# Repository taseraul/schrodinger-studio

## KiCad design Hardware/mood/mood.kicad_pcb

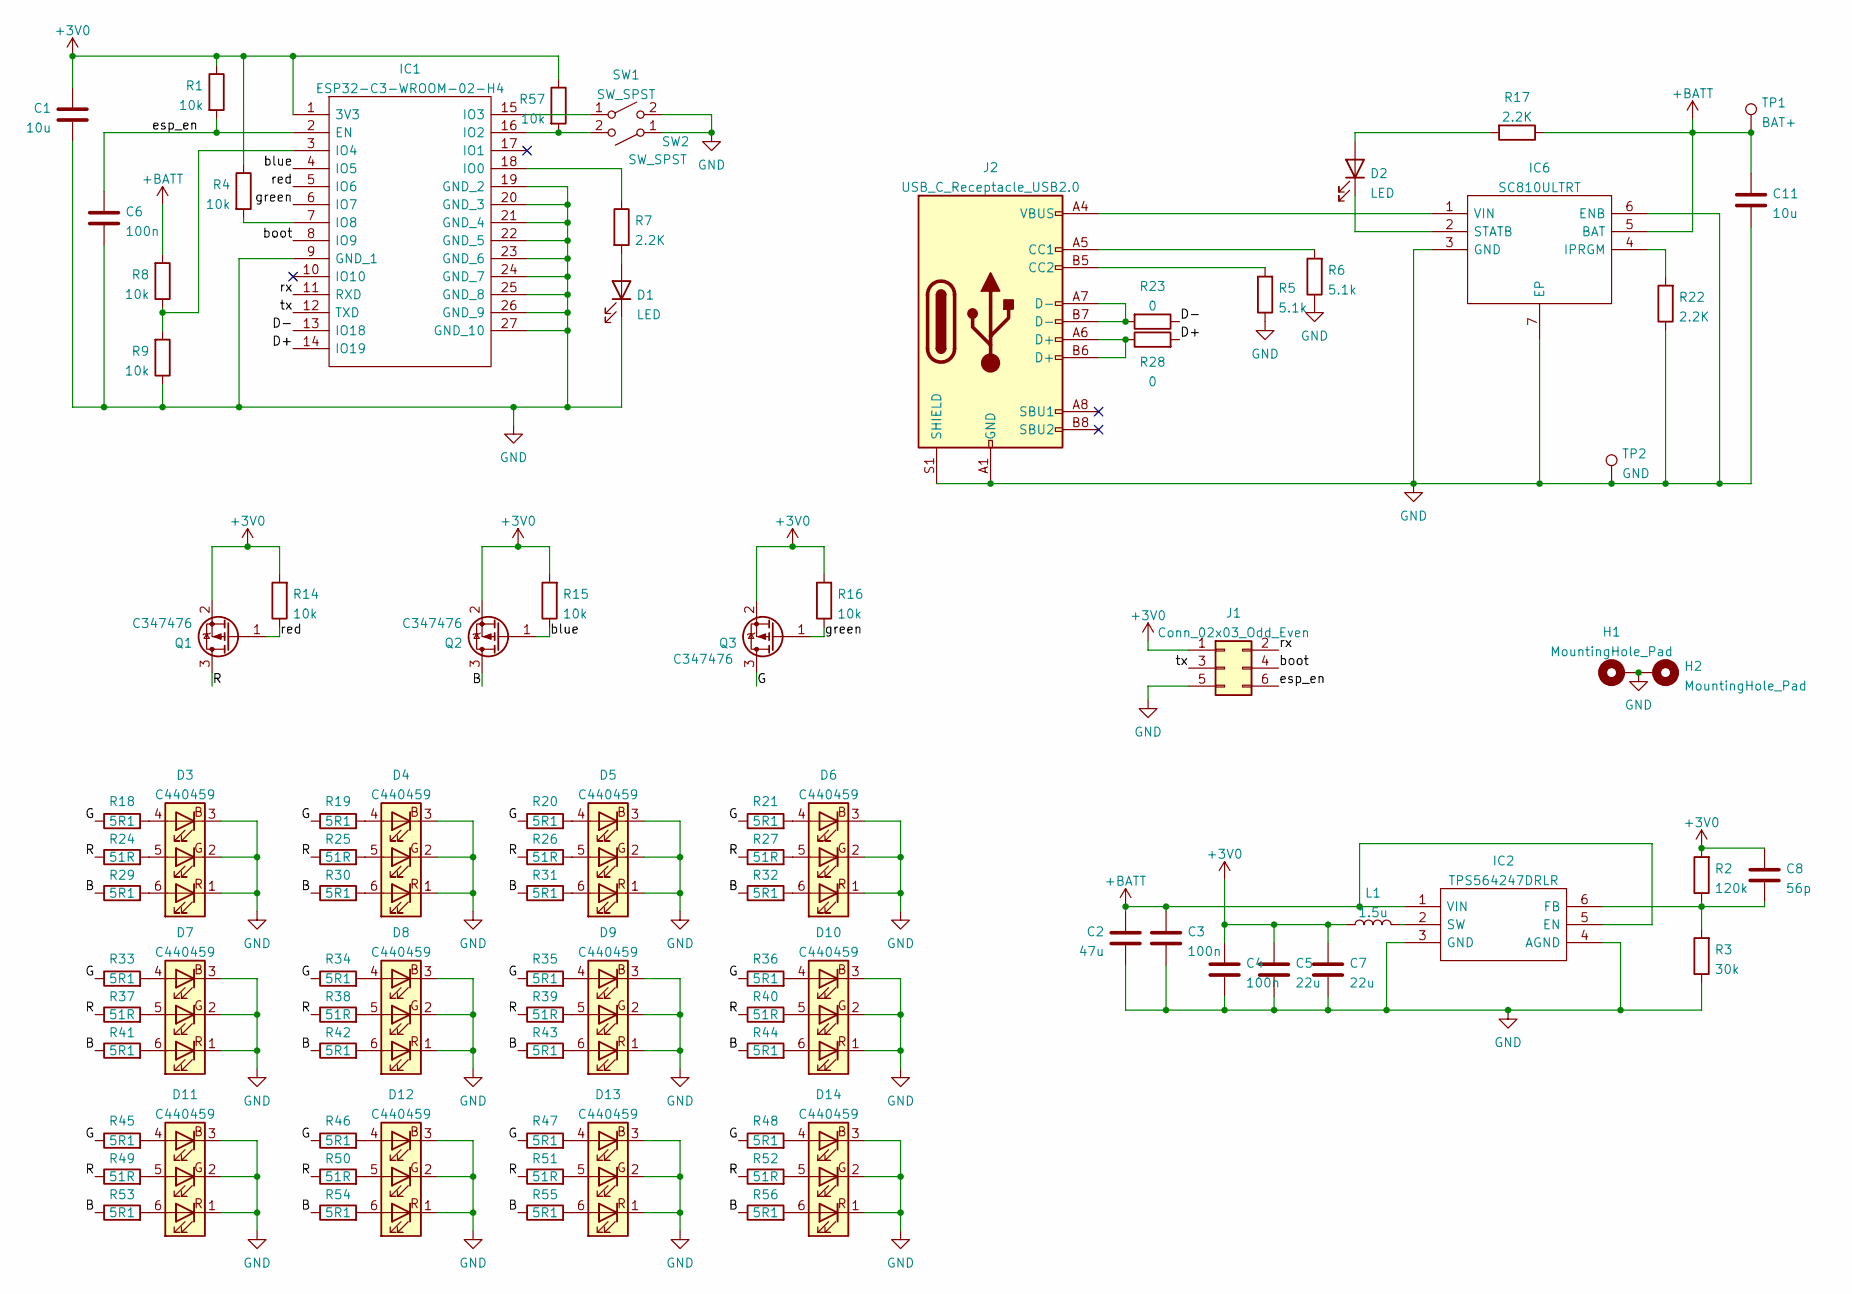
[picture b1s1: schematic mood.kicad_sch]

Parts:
C1, C11: 10u; C_0603_1608Metric_Pad1.08x0.95mm_HandSolder
C2: 47u; C_0805_2012Metric
C3, C4, C6: 100n; C_0603_1608Metric_Pad1.08x0.95mm_HandSolder
C5, C7: 22u; C_0805_2012Metric
C8: 56p; C_0603_1608Metric_Pad1.08x0.95mm_HandSolder
D1, D2: LED; LED_0805_2012Metric_Pad1.15x1.40mm_HandSolder
D3, D4, D5, D6, D7, D8, D9, D10, D11, D12, D13, D14: C440459; LED_RGB_5050-6
H1, H2: MountingHole_Pad; MountingHole_3.2mm_M3_DIN965_Pad
IC1: ESP32-C3-WROOM-02-H4; ESP32C3WROOM02H4; Manufacturer_Part_Number ESP32-C3-WROOM-02-H4; Mouser Part Number 356-ESP32C3WROOM02H4
IC2: TPS564247DRLR; SOT50P160X60-6N; Mouser Part Number 595-TPS564247DRLR
IC6: SC810ULTRT; SON50P200X200X60-7N-D; Mouser Part Number 947-SC810ULTRT
J1: Conn_02x03_Odd_Even; PinHeader_2x03_P2.54mm_Vertical
J2: USB_C_Receptacle_USB2.0; USB_C_Receptacle_Amphenol_12401610E4-2A_CircularHoles
L1: 1.5u; L_Wuerth_MAPI-4020
Q1, Q2, Q3: C347476; SOT-23
R1, R4, R8, R9, R14, R15, R16, R57: 10k; R_0603_1608Metric_Pad0.98x0.95mm_HandSolder
R2: 120k; R_0603_1608Metric_Pad0.98x0.95mm_HandSolder
R3: 30k; R_0603_1608Metric_Pad0.98x0.95mm_HandSolder
R5, R6: 5.1k; R_0603_1608Metric
R7, R17, R22: 2.2K; R_0603_1608Metric_Pad0.98x0.95mm_HandSolder
R18, R19, R20, R21, R29, R30, R31, R32, R33, R34, R35, R36, R41, R42, R43, R44, R45, R46, R47, R48, R53, R54, R55, R56: 5R1; R_0402_1005Metric_Pad0.72x0.64mm_HandSolder
R23, R28: 0; R_0603_1608Metric_Pad0.98x0.95mm_HandSolder
R24, R25, R26, R27, R37, R38, R39, R40, R49, R50, R51, R52: 51R; R_0402_1005Metric_Pad0.72x0.64mm_HandSolder
SW1, SW2: SW_SPST; SW_PUSH_6mm_H4.3mm
TP1: BAT+; TestPoint_Pad_4.0x4.0mm
TP2: GND; TestPoint_Pad_4.0x4.0mm

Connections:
+3V0: C1.1, C4.1, C5.1, C7.1, C8.1, IC1.1 (3V3), J1.1, L1.1, Q1.2 (S), Q2.2 (S), Q3.2 (S), R1.1, R2.2, R4.1, R14.2, R15.2, R16.2, R57.1
+BATT: C2.1, C3.1, C11.1, IC2.1 (VIN), IC2.5 (EN), IC6.5 (BAT), R8.2, R17.1, TP1.1
/B: Q2.3 (D), R29.1, R30.1, R31.1, R32.1, R41.1, R42.1, R43.1, R44.1, R53.1, R54.1, R55.1, R56.1
/D+: IC1.14 (IO19), R28.2
/D-: IC1.13 (IO18), R23.1
/G: Q3.3 (D), R18.1, R19.1, R20.1, R21.1, R33.1, R34.1, R35.1, R36.1, R45.1, R46.1, R47.1, R48.1
/R: Q1.3 (D), R24.1, R25.1, R26.1, R27.1, R37.1, R38.1, R39.1, R40.1, R49.1, R50.1, R51.1, R52.1
/blue: IC1.4 (IO5), Q2.1 (G), R15.1
/boot: IC1.8 (IO9), J1.4
/esp_en: C6.1, IC1.2 (EN), J1.6, R1.2
/green: IC1.6 (IO7), Q3.1 (G), R16.1
/red: IC1.5 (IO6), Q1.1 (G), R14.1
/rx: IC1.11 (RXD), J1.2
/tx: IC1.12 (TXD), J1.3
GND: C1.2, C2.2, C3.2, C4.2, C5.2, C6.2, C7.2, C11.2, D1.1 (K), D3.1 (RK), D3.2 (GK), D3.3 (BK), D4.1 (RK), D4.2 (GK), D4.3 (BK), D5.1 (RK), D5.2 (GK), D5.3 (BK), D6.1 (RK), D6.2 (GK), D6.3 (BK), D7.1 (RK), D7.2 (GK), D7.3 (BK), D8.1 (RK), D8.2 (GK), D8.3 (BK), D9.1 (RK), D9.2 (GK), D9.3 (BK), D10.1 (RK), D10.2 (GK), D10.3 (BK), D11.1 (RK), D11.2 (GK), D11.3 (BK), D12.1 (RK), D12.2 (GK), D12.3 (BK), D13.1 (RK), D13.2 (GK), D13.3 (BK), D14.1 (RK), D14.2 (GK), D14.3 (BK), H1.1, H2.1, IC1.9 (GND_1), IC1.19 (GND_2), IC1.20 (GND_3), IC1.21 (GND_4), IC1.22 (GND_5), IC1.23 (GND_6), IC1.24 (GND_7), IC1.25 (GND_8), IC1.26 (GND_9), IC1.27 (GND_10), IC2.3 (GND), IC2.4 (AGND), IC6.3 (GND), IC6.6 (ENB), IC6.7 (EP), J1.5, J2.A1 (GND), J2.A12 (GND), J2.B1 (GND), J2.B12 (GND), J2.S1 (SHIELD), R3.1, R5.1, R6.1, R9.1, R22.1, SW1.2 (B), SW2.1 (A), TP2.1
unnamed: C8.2, IC2.6 (FB), R2.1, R3.2
unnamed: D1.2 (A), R7.2
unnamed: D2.1 (K), IC6.2 (STATB)
unnamed: D2.2 (A), R17.2
unnamed: D3.4 (BA), R18.2
unnamed: D3.5 (GA), R24.2
unnamed: D3.6 (RA), R29.2
unnamed: D4.4 (BA), R19.2
unnamed: D4.5 (GA), R25.2
unnamed: D4.6 (RA), R30.2
unnamed: D5.4 (BA), R20.2
unnamed: D5.5 (GA), R26.2
unnamed: D5.6 (RA), R31.2
unnamed: D6.4 (BA), R21.2
unnamed: D6.5 (GA), R27.2
unnamed: D6.6 (RA), R32.2
unnamed: D7.4 (BA), R33.2
unnamed: D7.5 (GA), R37.2
unnamed: D7.6 (RA), R41.2
unnamed: D8.4 (BA), R34.2
unnamed: D8.5 (GA), R38.2
unnamed: D8.6 (RA), R42.2
unnamed: D9.4 (BA), R35.2
unnamed: D9.5 (GA), R39.2
unnamed: D9.6 (RA), R43.2
unnamed: D10.4 (BA), R36.2
unnamed: D10.5 (GA), R40.2
unnamed: D10.6 (RA), R44.2
unnamed: D11.4 (BA), R45.2
unnamed: D11.5 (GA), R49.2
unnamed: D11.6 (RA), R53.2
unnamed: D12.4 (BA), R46.2
unnamed: D12.5 (GA), R50.2
unnamed: D12.6 (RA), R54.2
unnamed: D13.4 (BA), R47.2
unnamed: D13.5 (GA), R51.2
unnamed: D13.6 (RA), R55.2
unnamed: D14.4 (BA), R48.2
unnamed: D14.5 (GA), R52.2
unnamed: D14.6 (RA), R56.2
unnamed: IC1.3 (IO4), R8.1, R9.2
unnamed: IC1.7 (IO8), R4.2
unnamed: IC1.15 (IO3), SW1.1 (A)
unnamed: IC1.16 (IO2), R57.2, SW2.2 (B)
unnamed: IC1.18 (IO0), R7.1
unnamed: IC2.2 (SW), L1.2
unnamed: IC6.1 (VIN), J2.A4 (VBUS), J2.A9 (VBUS), J2.B4 (VBUS), J2.B9 (VBUS)
unnamed: IC6.4 (IPRGM), R22.2
unnamed: J2.A5 (CC1), R6.2
unnamed: J2.A6 (D+), J2.B6 (D+), R28.1
unnamed: J2.A7 (D-), J2.B7 (D-), R23.2
unnamed: J2.B5 (CC2), R5.2

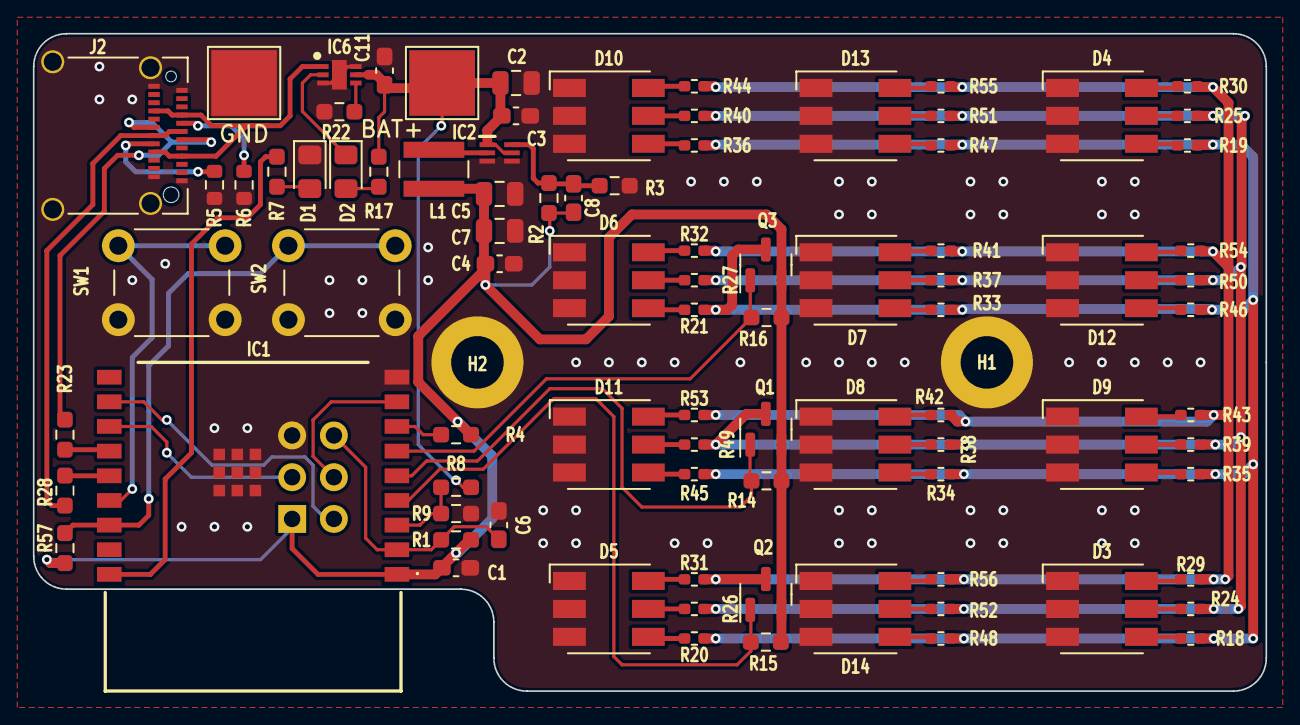
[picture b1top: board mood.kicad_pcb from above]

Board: 2 copper layers, 75.0 x 40.0 mm, 91 parts (1 on the bottom side), 67 nets.

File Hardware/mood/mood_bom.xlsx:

Id | Designator | Package | JLC
5.1k | R6,R5 | R_0603_1608Metric | C23186
22u | C7,C5 | C_0805_2012Metric | C59461
47u | C2 | C_0805_2012Metric | C16780
1.5u | L1 | L_Wuerth_MAPI-4020 | C135238
30k | R3 | R_0603_1608Metric_Pad0.98x0.95mm_HandSolder | C22984
120k | R2 | R_0603_1608Metric_Pad0.98x0.95mm_HandSolder | C25808
TPS564247DRLR | IC2 | SOT50P160X60-6N
56p | C8 | C_0603_1608Metric_Pad1.08x0.95mm_HandSolder | C39148
100n | C4,C3,C6 | C_0603_1608Metric_Pad1.08x0.95mm_HandSolder | C14663
51R | R52,R37,R51,R26,R24,R39,R40,R25,R27,R49,R38,R50 | R_0402_1005Metric_Pad0.72x0.64mm_HandSolder | C25125
5R1 | R30,R33,R31,R43,R47,R54,R35,R36,R56,R32,R21,R46,R55,R41,R19,R18,R42,R48,R34,R29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 | R_0402_1005Metric_Pad0.72x0.64mm_HandSolder | C25128
C440459 | D4,D10,D11,D8,D14,D5,D3,D9,D7,D12,D13,D6 | LED_RGB_5050-6 | C440459
ESP32-C3-WROOM-02-H4 | IC1 | ESP32C3WROOM02H4
0 | R28,R23 | R_0603_1608Metric_Pad0.98x0.95mm_HandSolder
USB_C_Receptacle_USB2.0 | J2 | USB_C_Receptacle_Amphenol_12401610E4-2A_CircularHoles
2.2K | R17,R7,R22 | R_0603_1608Metric_Pad0.98x0.95mm_HandSolder | C4190
BAT+ | TP1 | TestPoint_Pad_4.0x4.0mm
10k | R16,R1,R4,R14,R8,R57,R9,R15 | R_0603_1608Metric_Pad0.98x0.95mm_HandSolder | C25804
LED | D2,D1 | LED_0805_2012Metric_Pad1.15x1.40mm_HandSolder
10u | C11,C1 | C_0603_1608Metric_Pad1.08x0.95mm_HandSolder | C96446
GND | TP2 | TestPoint_Pad_4.0x4.0mm
C347476 | Q2,Q3,Q1 | SOT-23 | C347476
SC810ULTRT | IC6 | SON50P200X200X60-7N-D | C14663
MountingHole_Pad | H2,H1 | MountingHole_3.2mm_M3_DIN965_Pad
SW_SPST | SW2,SW1 | SW_PUSH_6mm_H4.3mm
Conn_02x03_Odd_Even | J1 | PinHeader_2x03_P2.54mm_Vertical

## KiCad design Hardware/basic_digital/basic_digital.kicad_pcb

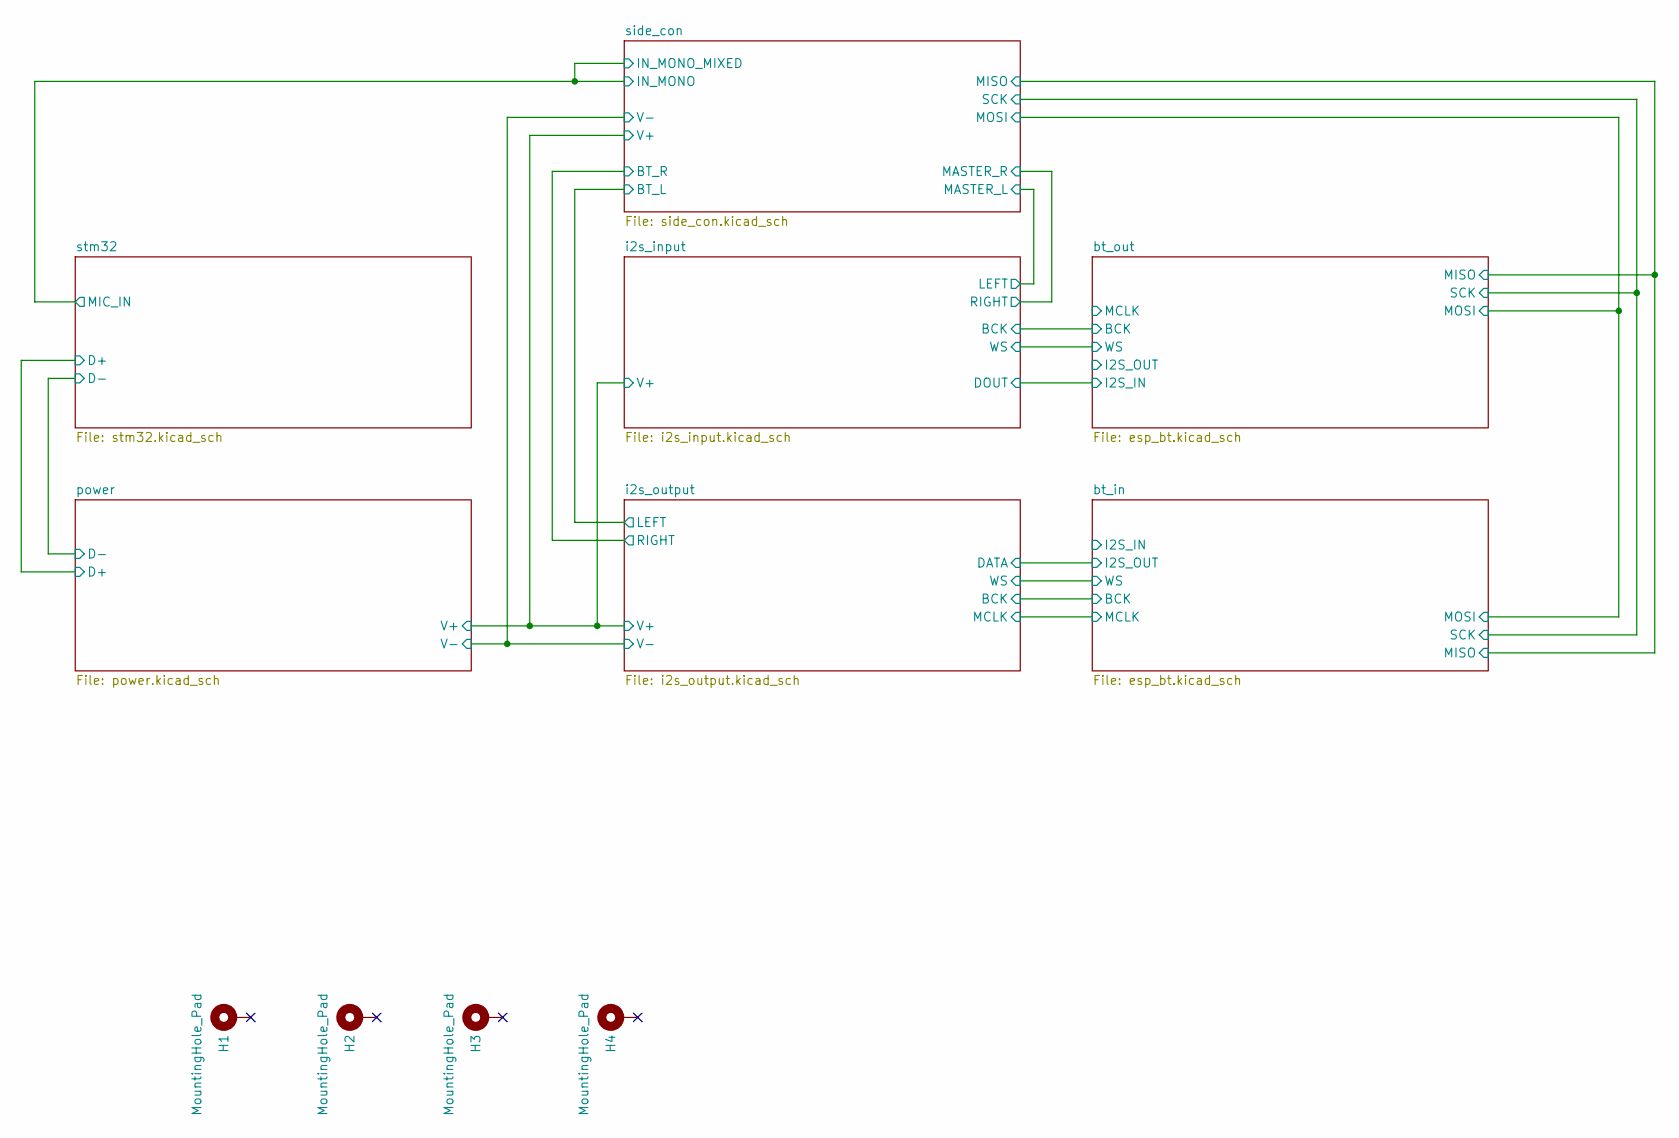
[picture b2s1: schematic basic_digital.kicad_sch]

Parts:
H1, H2, H3, H4: MountingHole_Pad; MountingHole_3.7mm_Pad

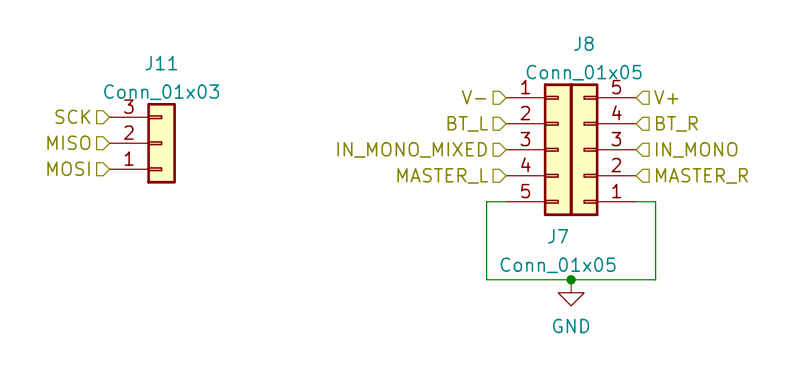
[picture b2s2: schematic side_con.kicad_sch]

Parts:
J7, J8: Conn_01x05; Harwin_M20-89005xx_1x05_P2.54mm_Horizontal
J11: Conn_01x03; Harwin_M20-89003xx_1x03_P2.54mm_Horizontal

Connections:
/bt_in/MISO: J11.2; also elsewhere on the board
/bt_in/MOSI: J11.1; also elsewhere on the board
/bt_in/SCK: J11.3; also elsewhere on the board
/i2s_input/LEFT: J7.4; also elsewhere on the board
/i2s_input/RIGHT: J8.2; also elsewhere on the board
/i2s_input/V+: J8.5; also elsewhere on the board
/i2s_output/LEFT: J7.2; also elsewhere on the board
/i2s_output/RIGHT: J8.4; also elsewhere on the board
/i2s_output/V-: J7.1; also elsewhere on the board
/side_con/IN_MONO: J7.3, J8.3; also elsewhere on the board

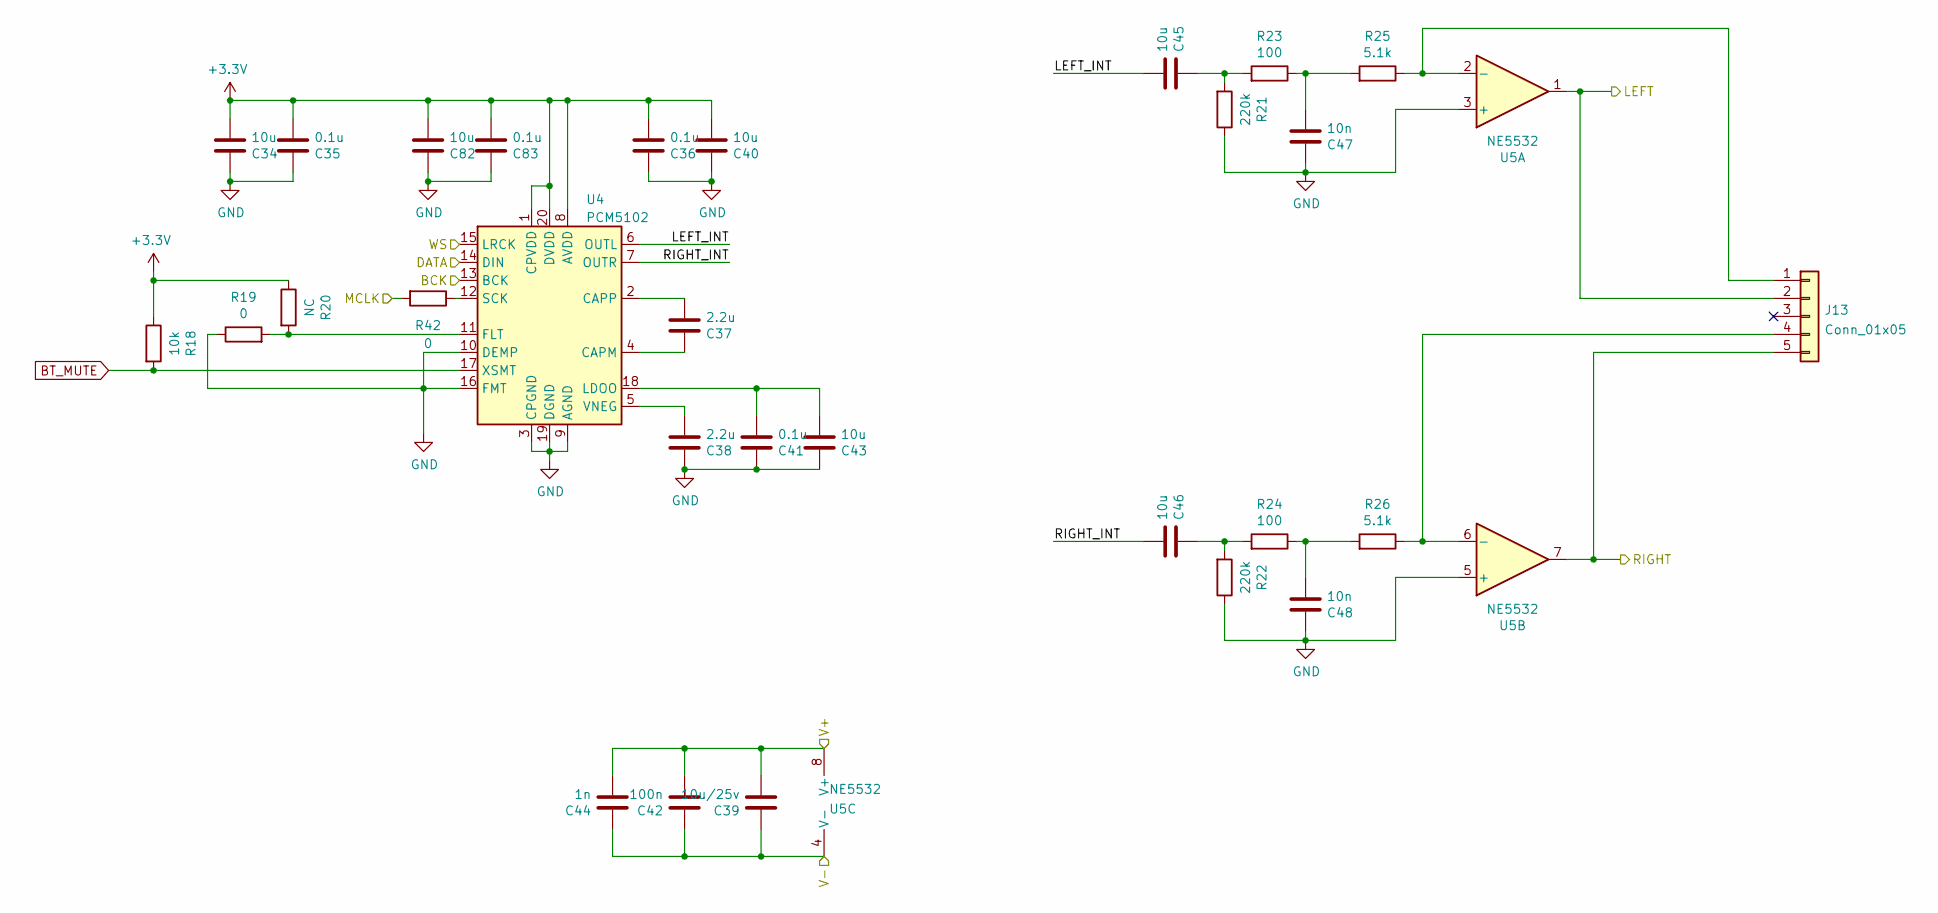
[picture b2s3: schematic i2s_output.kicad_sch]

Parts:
C34, C40, C43, C45, C46, C82: 10u; C_0603_1608Metric
C35, C36, C41, C83: 0.1u; C_0603_1608Metric
C37, C38: 2.2u; C_0603_1608Metric
C39: 10u/25v; C_0805_2012Metric
C42: 100n; C_0603_1608Metric
C44: 1n; C_0603_1608Metric
C47, C48: 10n; C_0603_1608Metric
J13: Conn_01x05; Harwin_M20-89005xx_1x05_P2.54mm_Horizontal
R18: 10k; R_0603_1608Metric
R19, R42: 0; R_0603_1608Metric
R20: NC; R_0603_1608Metric
R21, R22: 220k; R_0603_1608Metric
R23, R24: 100; R_0603_1608Metric
R25, R26: 5.1k; R_0603_1608Metric
U4: PCM5102; TSSOP-20_4.4x6.5mm_P0.65mm
U5: NE5532; SOIC-8_3.9x4.9mm_P1.27mm

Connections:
+3V3: C34.2, C35.2, C36.2, C40.2, C82.2, C83.2, R18.1, R20.1, U4.1 (CPVDD), U4.8 (AVDD), U4.20 (DVDD); also elsewhere on the board
/bt_in/BCK: U4.13 (BCK); also elsewhere on the board
/bt_in/I2S_OUT: U4.14 (DIN); also elsewhere on the board
/bt_in/WS: U4.15 (LRCK); also elsewhere on the board
/bt_in/boot: R42.2; also elsewhere on the board
/i2s_input/V+: C39.2, C42.2, C44.2, U5.8 (V+); also elsewhere on the board
/i2s_output/LEFT: J13.2, U5.1; also elsewhere on the board
/i2s_output/LEFT_INT: C45.2, U4.6 (OUTL)
/i2s_output/RIGHT: J13.5, U5.7; also elsewhere on the board
/i2s_output/RIGHT_INT: C46.2, U4.7 (OUTR)
/i2s_output/V-: C39.1, C42.1, C44.1, U5.4 (V-); also elsewhere on the board
BT_MUTE: R18.2, U4.17 (XSMT); also elsewhere on the board
unnamed: C37.1, U4.4 (CAPM)
unnamed: C37.2, U4.2 (CAPP)
unnamed: C38.2, U4.5 (VNEG)
unnamed: C41.2, C43.2, U4.18 (LDOO)
unnamed: C45.1, R21.2, R23.2
unnamed: C46.1, R22.2, R24.2
unnamed: C47.2, R23.1, R25.2
unnamed: C48.2, R24.1, R26.2
unnamed: J13.1, R25.1, U5.2 (-)
unnamed: J13.4, R26.1, U5.6 (-)
unnamed: R19.2, R20.2, U4.11 (FLT)
unnamed: R42.1, U4.12 (SCK)

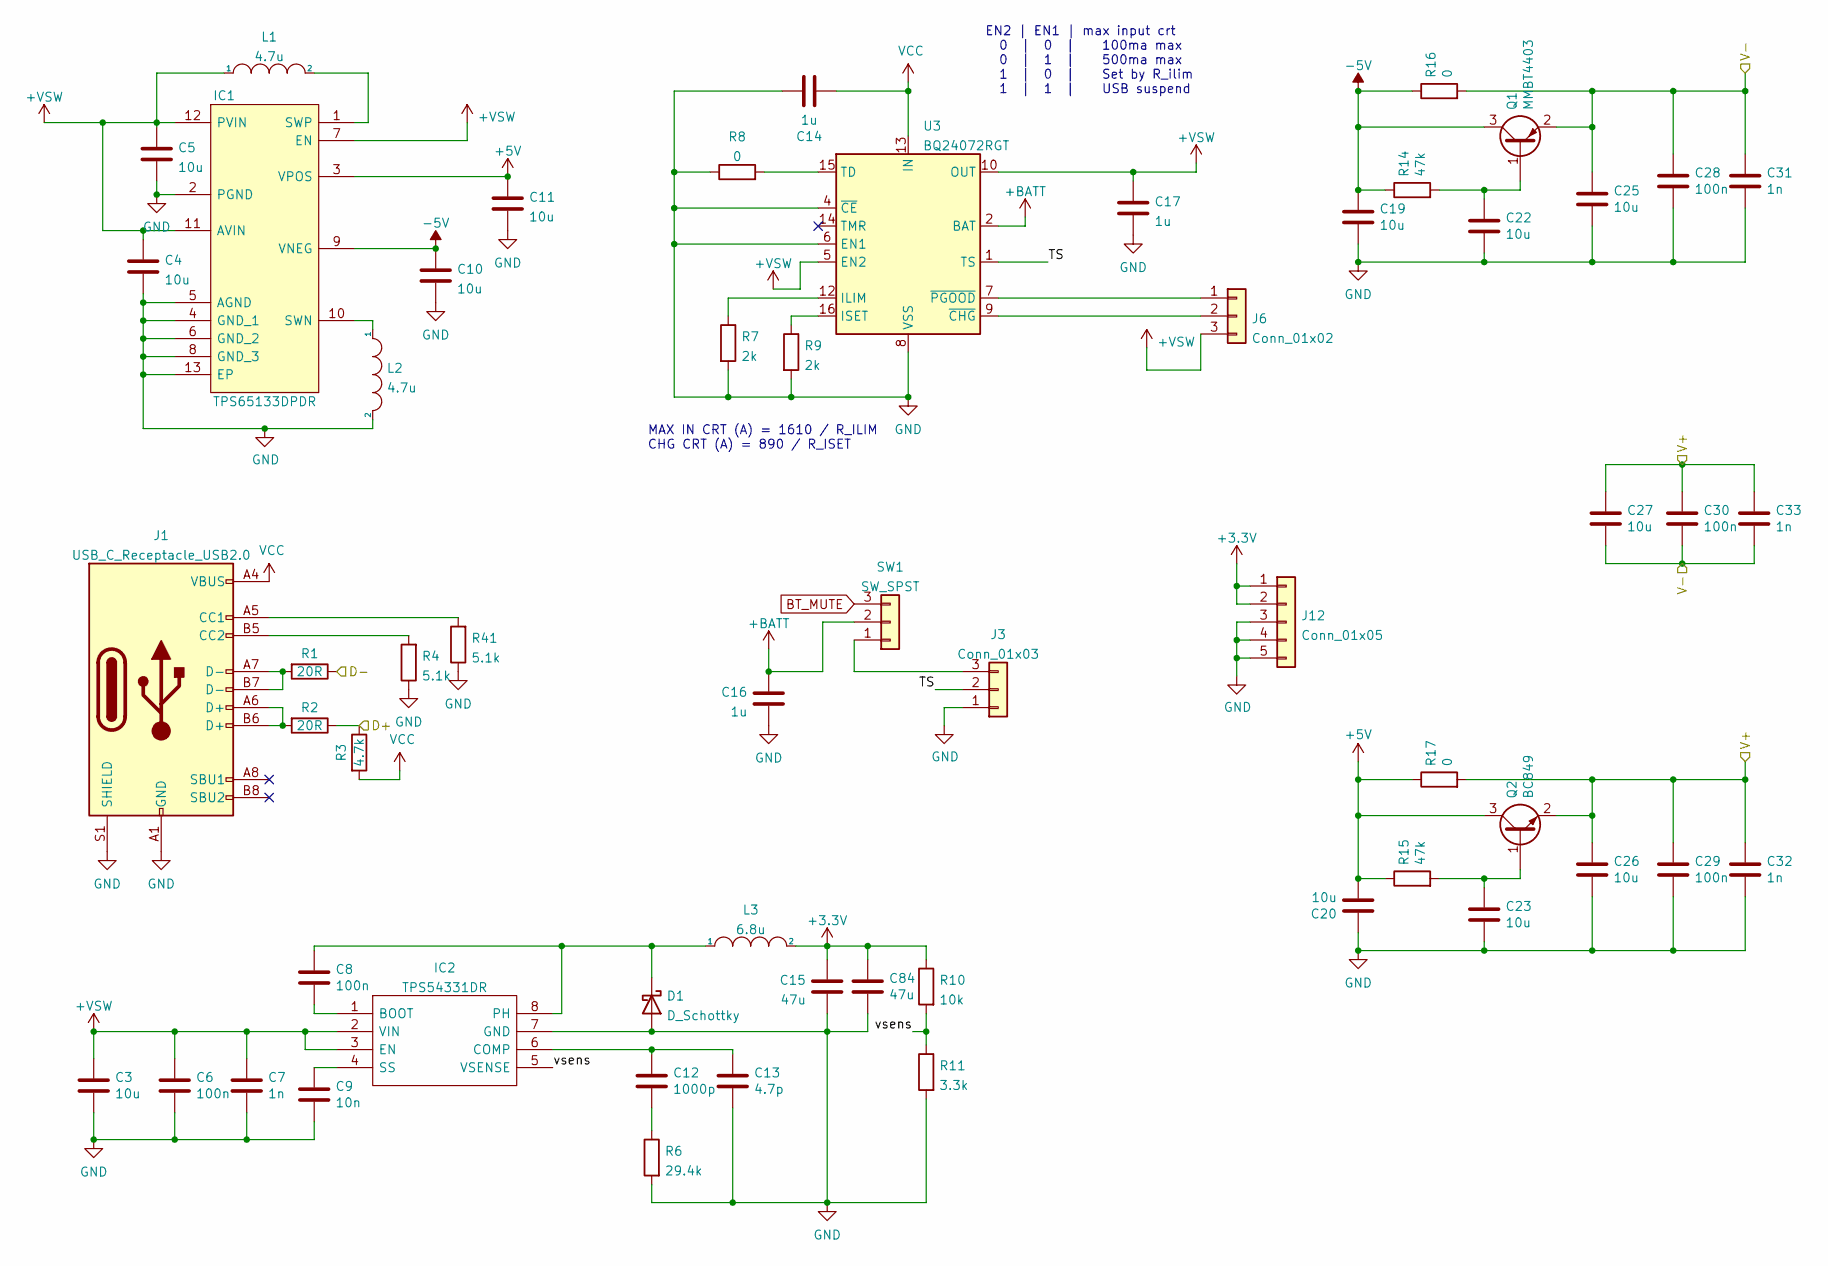
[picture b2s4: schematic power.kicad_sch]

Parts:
C3, C4, C5, C10, C11, C19, C20, C22, C23, C25, C26, C27: 10u; C_0603_1608Metric
C6, C8, C28, C29, C30: 100n; C_0603_1608Metric
C7, C31, C32, C33: 1n; C_0603_1608Metric
C9: 10n; C_0603_1608Metric
C12: 1000p; C_0603_1608Metric
C13: 4.7p; C_0603_1608Metric
C14, C16, C17: 1u; C_0603_1608Metric
C15, C84: 47u; C_1206_3216Metric
D1: D_Schottky; D_SOD-123
IC1: TPS65133DPDR; SON45P300X300X80-13N-D; Mouser Part Number 595-TPS65133DPDR
IC2: TPS54331DR; SOIC127P600X175-8N; Mouser Part Number 595-TPS54331DR
J1: USB_C_Receptacle_USB2.0; USB_C_Receptacle_Amphenol_12401610E4-2A_CircularHoles
J3: Conn_01x03; Harwin_M20-89003xx_1x03_P2.54mm_Horizontal
J6: Conn_01x02; Harwin_M20-89003xx_1x03_P2.54mm_Horizontal
J12: Conn_01x05; Harwin_M20-89005xx_1x05_P2.54mm_Horizontal
L1, L2: 4.7u; L_Vishay_IHLP-1212
L3: 6.8u; L_7.3x7.3_H4.5
Q1: MMBT4403; SOT-23
Q2: BC849; SOT-23
R1, R2: 20R; R_0603_1608Metric
R3: 4.7k; R_0603_1608Metric
R4, R41: 5.1k; R_0603_1608Metric
R6: 29.4k; R_0603_1608Metric
R7, R9: 2k; R_0603_1608Metric
R8, R16, R17: 0; R_0603_1608Metric
R10: 10k; R_0603_1608Metric
R11: 3.3k; R_0603_1608Metric
R14, R15: 47k; R_0603_1608Metric
SW1: SW_SPST; Harwin_M20-89003xx_1x03_P2.54mm_Horizontal
U3: BQ24072RGT; VQFN-16-1EP_3x3mm_P0.5mm_EP1.6x1.6mm

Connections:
+3V3: C15.1, C84.1, J12.1, J12.2, L3.2, R10.1; also elsewhere on the board
+5V: C11.1, C20.2, IC1.3 (VPOS), Q2.3 (C), R15.1, R17.1
+BATT: C16.2, SW1.2, U3.2 (BAT), U3.3 (BAT)
+VSW: C3.1, C4.1, C5.1, C6.1, C7.1, C17.1, IC1.7 (EN), IC1.11 (AVIN), IC1.12 (PVIN), IC2.2 (VIN), IC2.3 (EN), J6.3, L1.1, U3.5 (EN2), U3.10 (OUT), U3.11 (OUT)
-5V: C10.1, C19.1, IC1.9 (VNEG), Q1.3 (C), R14.1, R16.1
/i2s_input/V+: C26.1, C27.1, C29.1, C30.1, C32.1, C33.1, Q2.2 (E), R17.2; also elsewhere on the board
/i2s_output/V-: C25.1, C27.2, C28.1, C30.2, C31.1, C33.2, Q1.2 (E), R16.2; also elsewhere on the board
/power/D+: R2.1, R3.1; also elsewhere on the board
/power/D-: R1.1; also elsewhere on the board
/power/TS: J3.2, U3.1 (TS)
/power/vsens: IC2.5 (VSENSE), R10.2, R11.1
BT_MUTE: SW1.3; also elsewhere on the board
unnamed: C8.1, D1.1 (K), IC2.8 (PH), L3.1
unnamed: C8.2, IC2.1 (BOOT)
unnamed: C9.1, IC2.4 (SS)
unnamed: C12.1, C13.1, IC2.6 (COMP)
unnamed: C12.2, R6.1
unnamed: C22.1, Q1.1 (B), R14.2
unnamed: C23.1, Q2.1 (B), R15.2
unnamed: IC1.1 (SWP), L1.2
unnamed: IC1.10 (SWN), L2.1
unnamed: J1.A5 (CC1), R41.2
unnamed: J1.A6 (D+), J1.B6 (D+), R2.2
unnamed: J1.A7 (D-), J1.B7 (D-), R1.2
unnamed: J1.B5 (CC2), R4.2
unnamed: J3.3, SW1.1
unnamed: J6.1, U3.7 (~PGOOD)
unnamed: J6.2, U3.9 (~CHG)
unnamed: R7.1, U3.12 (ILIM)
unnamed: R8.2, U3.15 (TD)
unnamed: R9.1, U3.16 (ISET)
VCC: C14.2, J1.A4 (VBUS), J1.A9 (VBUS), J1.B4 (VBUS), J1.B9 (VBUS), R3.2, U3.13 (IN)

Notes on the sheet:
MAX IN CRT (A) = 1610 / R_ILIM CHG CRT (A) = 890 / R_ISET
EN2 | EN1 | max input crt 0 | 0 | 100ma max 0 | 1 | 500ma max 1 | 0 | Set by R_ilim 1 | 1 | USB suspend

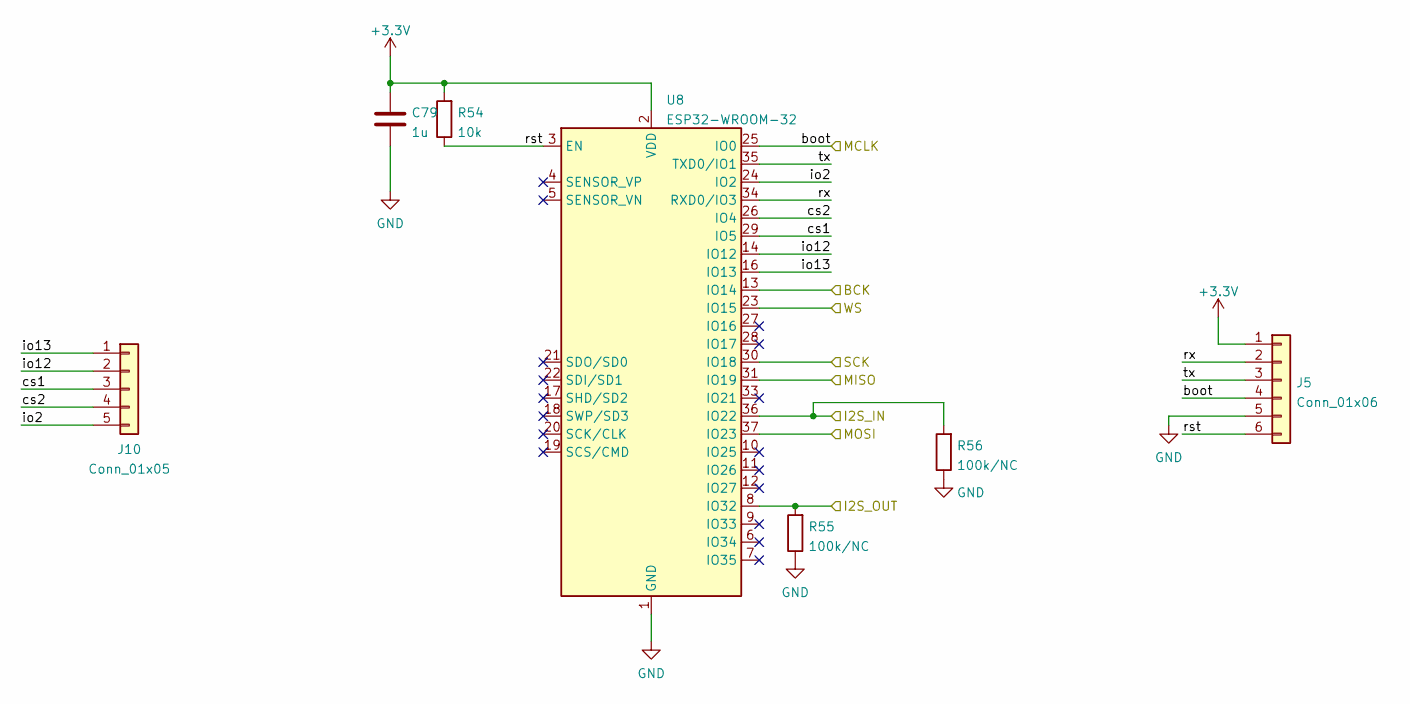
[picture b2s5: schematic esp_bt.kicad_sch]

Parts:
C79: 1u; C_0603_1608Metric
J5: Conn_01x06; PinHeader_2x03_P2.54mm_Vertical
J10: Conn_01x05; Harwin_M20-89005xx_1x05_P2.54mm_Horizontal
R54: 10k; R_0603_1608Metric
R55, R56: 100k/NC; R_0603_1608Metric
U8: ESP32-WROOM-32

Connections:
+3V3: C79.1, J5.1, R54.2, U8.2 (VDD); also elsewhere on the board
/bt_in/MISO: U8.31 (IO19); also elsewhere on the board
/bt_in/MOSI: U8.37 (IO23); also elsewhere on the board
/bt_in/SCK: U8.30 (IO18); also elsewhere on the board
/bt_out/BCK: U8.13 (IO14); also elsewhere on the board
/bt_out/I2S_IN: R56.2, U8.36 (IO22); also elsewhere on the board
/bt_out/I2S_OUT: R55.2, U8.8 (IO32)
/bt_out/WS: U8.23 (IO15); also elsewhere on the board
/bt_out/boot: J5.4, U8.25 (IO0)
/bt_out/cs1: J10.3, U8.29 (IO5)
/bt_out/cs2: J10.4, U8.26 (IO4)
/bt_out/io2: J10.5, U8.24 (IO2)
/bt_out/io12: J10.2, U8.14 (IO12)
/bt_out/io13: J10.1, U8.16 (IO13)
/bt_out/rst: J5.6, R54.1, U8.3 (EN)
/bt_out/rx: J5.2, U8.34 (RXD0/IO3)
/bt_out/tx: J5.3, U8.35 (TXD0/IO1)

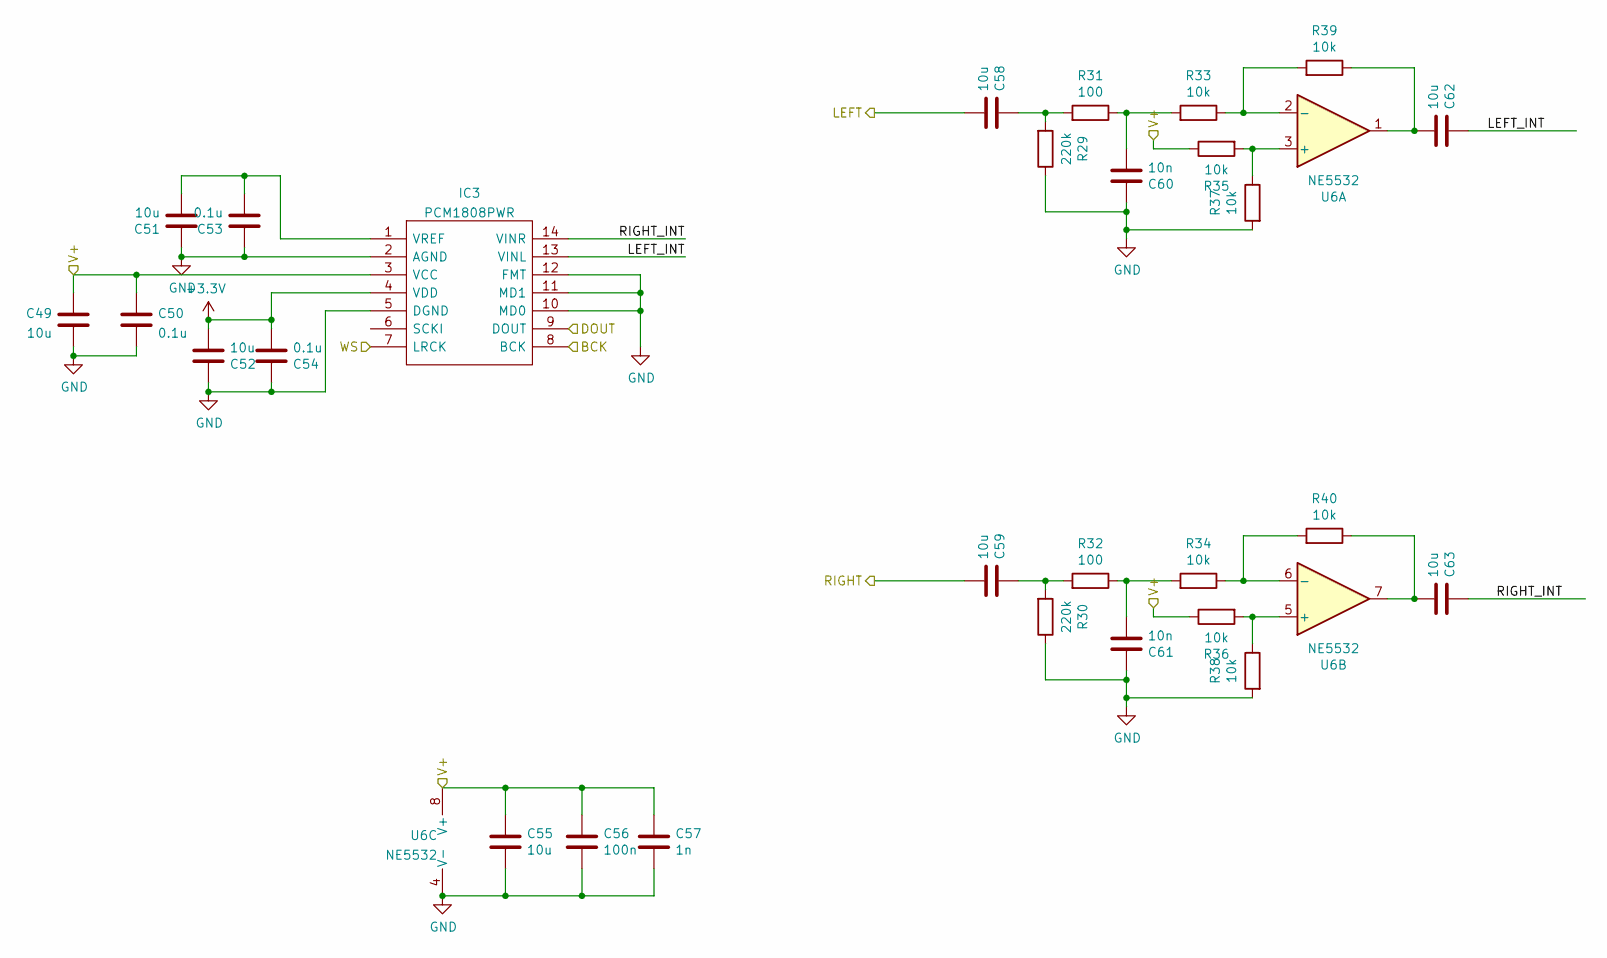
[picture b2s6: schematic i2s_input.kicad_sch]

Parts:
C49, C51, C52, C55, C58, C59, C62, C63: 10u; C_0603_1608Metric
C50, C53, C54: 0.1u; C_0603_1608Metric
C56: 100n; C_0603_1608Metric
C57: 1n; C_0603_1608Metric
C60, C61: 10n; C_0603_1608Metric
IC3: PCM1808PWR; Mouser Part Number 595-PCM1808PWR
R29, R30: 220k; R_0603_1608Metric
R31, R32: 100; R_0603_1608Metric
R33, R34, R35, R36, R37, R38, R39, R40: 10k; R_0603_1608Metric
U6: NE5532; SOIC-8_3.9x4.9mm_P1.27mm

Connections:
+3V3: C52.2, C54.2, IC3.4 (VDD); also elsewhere on the board
/bt_out/BCK: IC3.8 (BCK); also elsewhere on the board
/bt_out/I2S_IN: IC3.9 (DOUT); also elsewhere on the board
/bt_out/WS: IC3.7 (LRCK); also elsewhere on the board
/i2s_input/LEFT: C58.2; also elsewhere on the board
/i2s_input/LEFT_INT: C62.1, IC3.13 (VINL)
/i2s_input/RIGHT: C59.2; also elsewhere on the board
/i2s_input/RIGHT_INT: C63.1, IC3.14 (VINR)
/i2s_input/V+: C49.2, C50.2, C55.1, C56.1, C57.1, IC3.3 (VCC), R35.1, R36.1, U6.8 (V+); also elsewhere on the board
unnamed: C51.2, C53.2, IC3.1 (VREF)
unnamed: C58.1, R29.2, R31.2
unnamed: C59.1, R30.2, R32.2
unnamed: C60.2, R31.1, R33.2
unnamed: C61.2, R32.1, R34.2
unnamed: C62.2, R39.1, U6.1
unnamed: C63.2, R40.1, U6.7
unnamed: R33.1, R39.2, U6.2 (-)
unnamed: R34.1, R40.2, U6.6 (-)
unnamed: R35.2, R37.1, U6.3 (+)
unnamed: R36.2, R38.1, U6.5 (+)
